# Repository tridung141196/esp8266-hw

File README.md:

# esp8266_iotmaker

## Features

ESP8266 IOTMAKERVN:
- Size: 1.86x1 inch.
- Intergrate micro USB.
- Input Voltage: 5v (Vusb).
- Open hardware with CC-BY-SA license.
- Design with KiCad.

## Hardware

### Schematics

### PCB Layout

### 3D

### Pinout 

### Fritzing part 

### Gerber

[Download](./assets/esp8266-1x1.86inch.zip)

### BOM 

| Designator | Package | Quantity | Designation  | Nơi bán  |
|-------------------------|--------------------------------|----------|--------------|--------------|
| U1                      | USB_Micro-B                    | 1        | usb_mini_b   |[thegioiic](http://thegioiic.com/products/microusb-fm-v2)|
| U2                      | QFN-32-1EP_5x5mm_Pitch0.5mm    | 1        | ESP8266ES    |    						       |
| U3                      | QFN-28-1EP_5x5mm_Pitch0.5mm    | 1        | CP2102       |[thegioiic](http://thegioiic.com/products/cp2102)        |
| U4                      | SOIC-8_3.9x4.9mm_Pitch1.27mm   | 1        | SLASH 4MB    |[banlinhkien](http://banlinhkien.vn/goods-5796-w25q32fv-sop8-ic-flash-32mbit.html) |
| U6                      | SOT-223                        | 1        | AMS1117/3V3  |[thegioiic](http://thegioiic.com/products/ams1117-3-3v)  |
| D1,D8                   | LED_0603                       | 2        | LED_Blue     |[thegioiic](http://thegioiic.com/products/bl-0603-led)   |
| Y1                      | Crystal_SMD_2016-4pin_2.0x1.6mm| 1        | 26MHz   |[thegioiic](http://thegioiic.com/products/26mhz-crystal-c5032)|
| Q1,Q2                   | SOT-23                         | 2        | S8050        |[banlinhkien](http://banlinhkien.vn/goods-4708-s8050-sot23-trans-npn-0-5a-40v-smd-j3y-.html)|
| L1,L2                   | L_0603                         | 2        |              |
| C1,C6,C9                | C_0603                         | 3        | 10uF      |[thegioiic](http://thegioiic.com/products/10uf-16v-0603-cap)|
| C3,C8,C10,C11,C13       | C_0603                         | 5        | 100nF    |[thegioiic](http://thegioiic.com/products/100nf-16v-0603-cap)|
| C5,C7                   | C_0603                         | 2        | 10pF     |[thegioiic](http://thegioiic.com/products/10pf-50v-0603-cap)|
| C12,C15                 | C_1206                         | 2        | 10uF Tant    |[lkbk](http://linhkienbachkhoa.com/san-pham/tu-tantalum-10uf-16v-1206-10-3ohm/)|
| C2                      | C_0603                         | 1        | 5,6pF        |[thegioiic](http://thegioiic.com/products/6-8pf-50v-0603-cap)|
| R1,R2,R4,R5,R6,R7,R8    | R_0603                         | 7        | 10K          |[thegioiic](http://thegioiic.com/products/10k-ohm-0603-1)|
| R9,R10,R11,R14,R15      | R_0603                         | 5        | 470R         |[thegioiic](http://thegioiic.com/products/470-ohm-0603-1)|
| R12                     | R_0603                         | 1        | 220k/1%     |[thegioiic](http://thegioiic.com/products/220k-ohm-0603-1)|
| R13                     | R_0603                         | 1        | 100k/1%     |[thegioiic](http://thegioiic.com/products/100k-ohm-0603-1)|
| R3                      | R_0603                         | 1        | 220R         |[thegioiic](http://thegioiic.com/products/220-ohm-0603-1)|
| R18                     | R_0603                         | 1        | 100R         |[thegioiic](http://thegioiic.com/products/100-ohm-0603-1)|
| R20                     | R_0603                         | 1        | 2k           |[thegioiic](http://thegioiic.com/products/2k-ohm-0603-1)|
| D5                      | D_SOD-123                      | 1        | 1N5819       |[banlinhkien](http://banlinhkien.vn/goods-5519-diode-s4-sod123-1n5819-sod123-.html)|
| SW1,SW2                 | SWITCH SMD                     | 2        | TACTICLE SW  |[thegioiic](http://thegioiic.com/products/ts-1189e)|
| J1,J2                   | Pin_Header_Straight_1x10       | 2        | CONN_01X10   |

### Remark

This project was in development phase - we will remove this remark after release

# License

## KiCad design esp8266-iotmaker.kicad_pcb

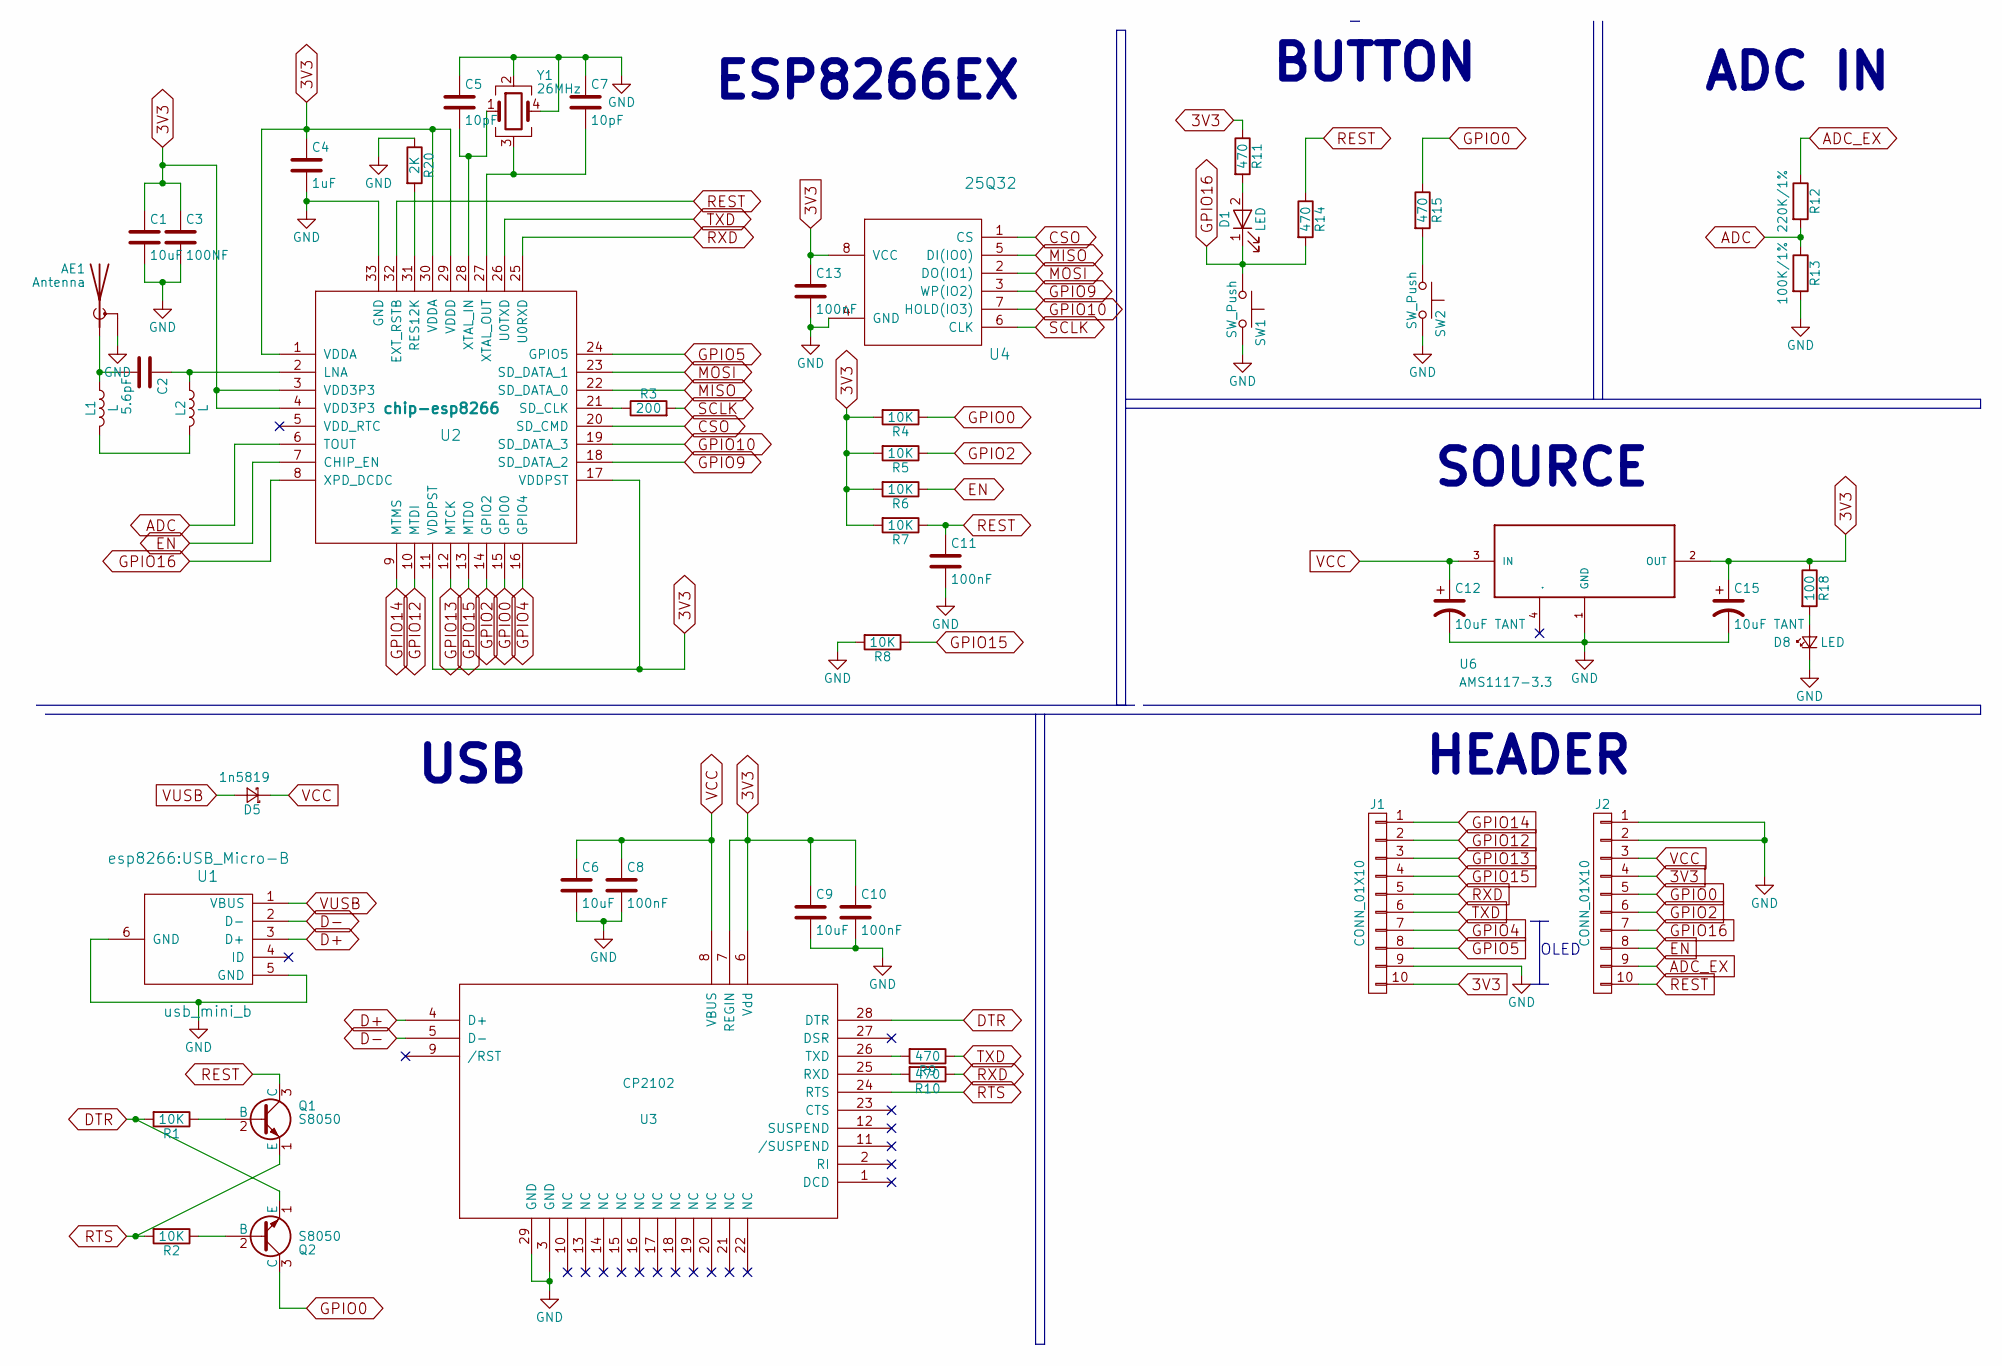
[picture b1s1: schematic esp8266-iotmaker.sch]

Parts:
AE1: Antenna; anten
C1, C6, C9: 10uF; C_0603
C2: 5.6pF; C_0603
C3: 100NF; C_0603
C4: 1uF; C_0603
C5, C7: 10pF; C_0603
C8, C10, C11, C13: 100nF; C_0603
C12, C15: 10uF TANT; C_1206
D1, D8: LED; LED_0603
D5: 1n5819; D_SOD-123
J1, J2: CONN_01X10; Pin_Header_Straight_1x10_Pitch2.54mm
L1, L2: L; L_0603
Q1, Q2: S8050; SOT-23_standar
R1, R2, R4, R5, R6, R7, R8: 10K; R_0603
R3: 200; R_0603
R9, R10, R11, R14, R15: 470; R_0603
R12: 220K/1%; R_0603
R13: 100K/1%; R_0603
R18: 100; R_0603
R20: 2K; R_0603
SW1, SW2: SW_Push; nut_nhan_ngang
U1: usb_mini_b; USB_Micro-B
U2: chip-esp8266; esp8266ex
U3: CP2102; cp2102
U4: 25Q32; SOIC-8_3.9x4.9mm_Pitch1.27mm
U6: AMS1117-3.3; SOT-223
Y1: 26MHz; Crystal_SMD_5032-4pin_5.0x3.2mm

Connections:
3V3: C1.1, C3.1, C4.1, C9.1, C10.1, C13.1, C15.1, J1.10, J2.4, R4.2, R5.2, R6.2, R7.2, R11.1, R18.1, U2.1 (VDDA), U2.3 (VDD3P3), U2.4 (VDD3P3), U2.11 (VDDPST), U2.17 (VDDPST), U2.29 (VDDD), U2.30 (VDDA), U3.6 (Vdd), U3.7 (REGIN), U4.8 (VCC), U6.2 (OUT)
ADC: R12.2, R13.1, U2.6 (TOUT)
ADC_EX: J2.9, R12.1
CSO: U2.20 (SD_CMD), U4.1 (CS)
D+: U1.3 (D+), U3.4 (D+)
D-: U1.2 (D-), U3.5 (D-)
DTR: Q2.1 (E), R1.2, U3.28 (DTR)
EN: J2.8, R6.1, U2.7 (CHIP_EN)
GND: AE1.2 (Shield), C1.2, C3.2, C4.2, C5.1, C6.2, C7.1, C8.2, C9.2, C10.2, C11.2, C12.2, C13.2, C15.2, D8.1 (K), J1.9, J2.1, J2.2, R8.2, R13.2, R20.1, SW1.2, SW2.2, U1.5 (GND), U1.6 (GND), U2.33 (GND), U3.3 (GND), U3.29 (GND), U4.4 (GND), U6.1 (GND), Y1.2, Y1.4; also elsewhere on the board
GPIO0: J2.5, Q2.3 (C), R4.1, R15.1, U2.15 (GPIO0)
GPIO2: J2.6, R5.1, U2.14 (GPIO2)
GPIO4: J1.7, U2.16 (GPIO4)
GPIO5: J1.8, U2.24 (GPIO5)
GPIO9: U2.18 (SD_DATA_2), U4.3 (WP(IO2))
GPIO10: U2.19 (SD_DATA_3), U4.7 (HOLD(IO3))
GPIO12: J1.2, U2.10 (MTDI)
GPIO13: J1.3, U2.12 (MTCK)
GPIO14: J1.1, U2.9 (MTMS)
GPIO15: J1.4, R8.1, U2.13 (MTD0)
GPIO16: D1.1 (K), J2.7, R14.2, SW1.1, U2.8 (XPD_DCDC)
MISO: U2.22 (SD_DATA_0), U4.5 (DI(IO0))
MOSI: U2.23 (SD_DATA_1), U4.2 (DO(IO1))
unnamed 22: AE1.1 (A), C2.2, L1.1; also elsewhere on the board
unnamed: C2.1, L2.1, U2.2 (LNA)
unnamed: C5.2, U2.28 (XTAL_IN), Y1.1
unnamed: C7.2, U2.27 (XTAL_OUT), Y1.3
unnamed: D1.2 (A), R11.2
unnamed: D8.2 (A), R18.2
unnamed: L1.2, L2.2
unnamed: Q1.2 (B), R1.1
unnamed: Q2.2 (B), R2.1
unnamed: R3.1, U2.21 (SD_CLK)
unnamed: R9.2, U3.26 (TXD)
unnamed: R10.2, U3.25 (RXD)
unnamed: R15.2, SW2.1
unnamed: R20.2, U2.31 (RES12K)
REST: C11.1, J2.10, Q1.3 (C), R7.1, R14.1, U2.32 (EXT_RSTB)
RTS: Q1.1 (E), R2.2, U3.24 (RTS)
RXD: J1.5, R10.1, U2.25 (U0RXD)
SCLK: R3.2, U4.6 (CLK)
TXD: J1.6, R9.1, U2.26 (U0TXD)
VCC: C6.1, C8.1, C12.1, D5.1 (K), J2.3, U3.8 (VBUS), U6.3 (IN)
VUSB: D5.2 (A), U1.1 (VBUS)

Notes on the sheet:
ESP8266EX
BUTTON
USB
SOURCE
HEADER
ADC IN
OLED

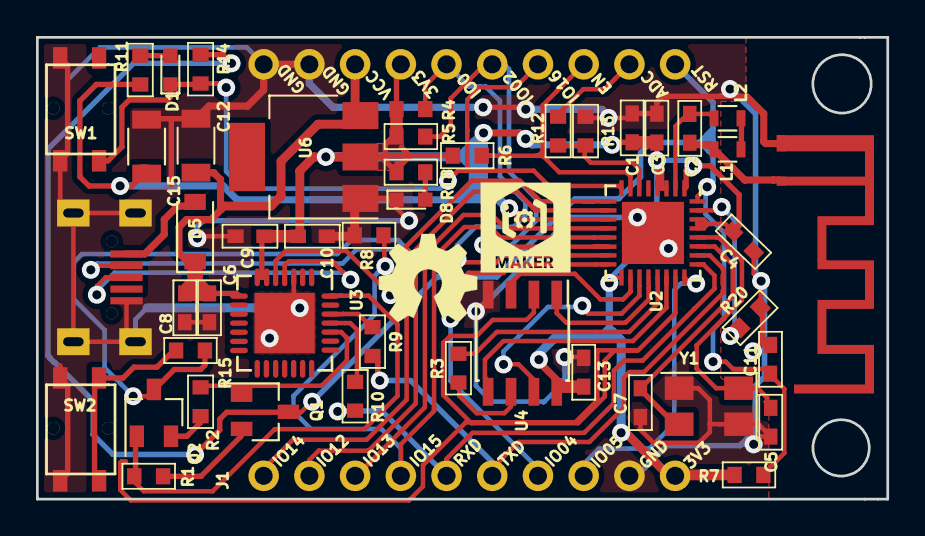
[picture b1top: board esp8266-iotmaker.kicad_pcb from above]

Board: 2 copper layers, 47.2 x 25.7 mm, 49 parts (0 on the bottom side), 43 nets.

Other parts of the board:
ANT: ANT; anten

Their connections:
GND: ANT.2; also elsewhere on the board
unnamed 22: ANT.1; also elsewhere on the board

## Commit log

2017-10-24 set up kicad
2017-10-25 edit schematic
2017-10-28 xap xep linh kien'
2017-10-28 add pcb
2017-10-30 update footprint
2017-10-30 add 3dshape
2017-11-01 complete pcb source
2017-11-03 xap xep linh kien
2017-11-04 complete pcb ver2.0
2017-11-05 add 3d and edit pcb
2017-11-05 edit readme
2017-11-05 edit solder mark
2017-11-11 edit pcb
2017-11-11 edit pcb with new crystal
2017-11-12 change footprint usb

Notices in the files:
README.md:
License:
http://mirrors.creativecommons.org/presskit/buttons/88x31/png/by-sa.png
